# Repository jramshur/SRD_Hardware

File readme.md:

# SRD Hardware

The simultaneous stimulation-and-recording device (SRD) is a wearable, wireless brain-computer interface system designed to train cortical circuits in awake rats. This repository contains design files for the SRD hardware including Eagle PCB files and 3D design files for the enclosure.

Software and firmware for this hardware system can be found in the following repositories:

- https://github.com/jramshur/SRD_Firmware
- https://github.com/jramshur/SRD_GUI

## Description

The simultaneous stimulation-and-recording device (SRD) is a Bluetooth wireless brain-computer interface system designed for use in awake rats. This repository contains design files for the SRD hardware including Eagle PCB files and 3D design files for the enclosure.

### Features
- Cypress Semiconductor PSoC 3 System-on-a-Chip 
- Intan Technologies digital electrophysiology interface chip
- more ...

### System Overview

## Wiki Navigation

* [Home][home]
* [Circuit Design][circuit]
* [PCB Design][pcb]
* [Enclosure][enclosure]
* [Battery][battery]
* [Programming Adaptor][adaptor]

[home]: https://github.com/jramshur/SRD_Hardware/wiki/Home
[circuit]: https://github.com/jramshur/SRD_Hardware/wiki/Circuit
[pcb]: https://github.com/jramshur/SRD_Hardware/wiki/PCB
[enclosure]: https://github.com/jramshur/SRD_Hardware/wiki/Enclosure
[battery]: https://github.com/jramshur/SRD_Hardware/wiki/Battery
[adaptor]: https://github.com/jramshur/SRD_Hardware/wiki/Programming-Adaptor

## Contact Info

John T. Ramshur, PhD  
jramshur@gmail.com  
LinkedIn: [http://www.linkedin.com/in/johnramshur](http://www.linkedin.com/in/johnramshur)  
Blog: [http://www.johnramshur.com](http://www.johnramshur.com)

**Project was part of my PhD work while at:**

Joint Program in Biomedical Engineering  
[University of Memphis](http://www.memphis.edu/bme/)  
[University of Tennessee Health Science Center](http://www.uthsc.edu/bme/)  
Advisor: Amy de Jongh Curry, PhD

Department of Anatomy and Neurobiology  
[University of Tennessee Health Science Center](https://www.uthsc.edu/anatomy-neurobiology/)  
Advisor: Robert S. Waters, PhD

## License

GNU General Public License 3.0

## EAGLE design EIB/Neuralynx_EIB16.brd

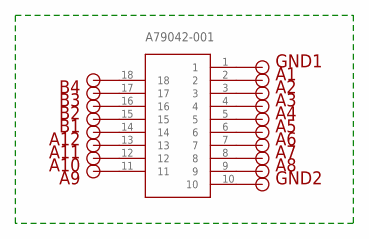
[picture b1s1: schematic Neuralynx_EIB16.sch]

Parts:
A1, A2, A3, A4, A5, A6, A7, A8, A9, A10, A11, A12: VIA_20MILL; VIA_20MIL
A79042-001: A79043-001; OMNETCS-18PIN-SMD
B1, B2, B3, B4: VIA_20MILL; VIA_20MIL
GND1, GND2: VIA_20MILL; VIA_20MIL

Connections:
unnamed: A79042-001.1, GND1.P$1
unnamed: A79042-001.10, GND2.P$1
unnamed: A8.P$1, A79042-001.9
unnamed: A7.P$1, A79042-001.8
unnamed: A6.P$1, A79042-001.7
unnamed: A5.P$1, A79042-001.6
unnamed: A4.P$1, A79042-001.5
unnamed: A3.P$1, A79042-001.4
unnamed: A2.P$1, A79042-001.3
unnamed: A1.P$1, A79042-001.2
unnamed: A9.P$1, A79042-001.11
unnamed: A10.P$1, A79042-001.12
unnamed: A12.P$1, A79042-001.14
unnamed: A79042-001.15, B1.P$1
unnamed: A79042-001.16, B2.P$1
unnamed: A79042-001.17, B3.P$1
unnamed: A79042-001.18, B4.P$1
unnamed: A11.P$1, A79042-001.13

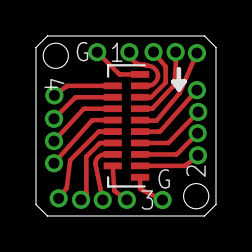
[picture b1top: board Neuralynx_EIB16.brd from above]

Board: 2 copper layers, 10.0 x 10.0 mm, 19 parts (0 on the bottom side), 18 nets.

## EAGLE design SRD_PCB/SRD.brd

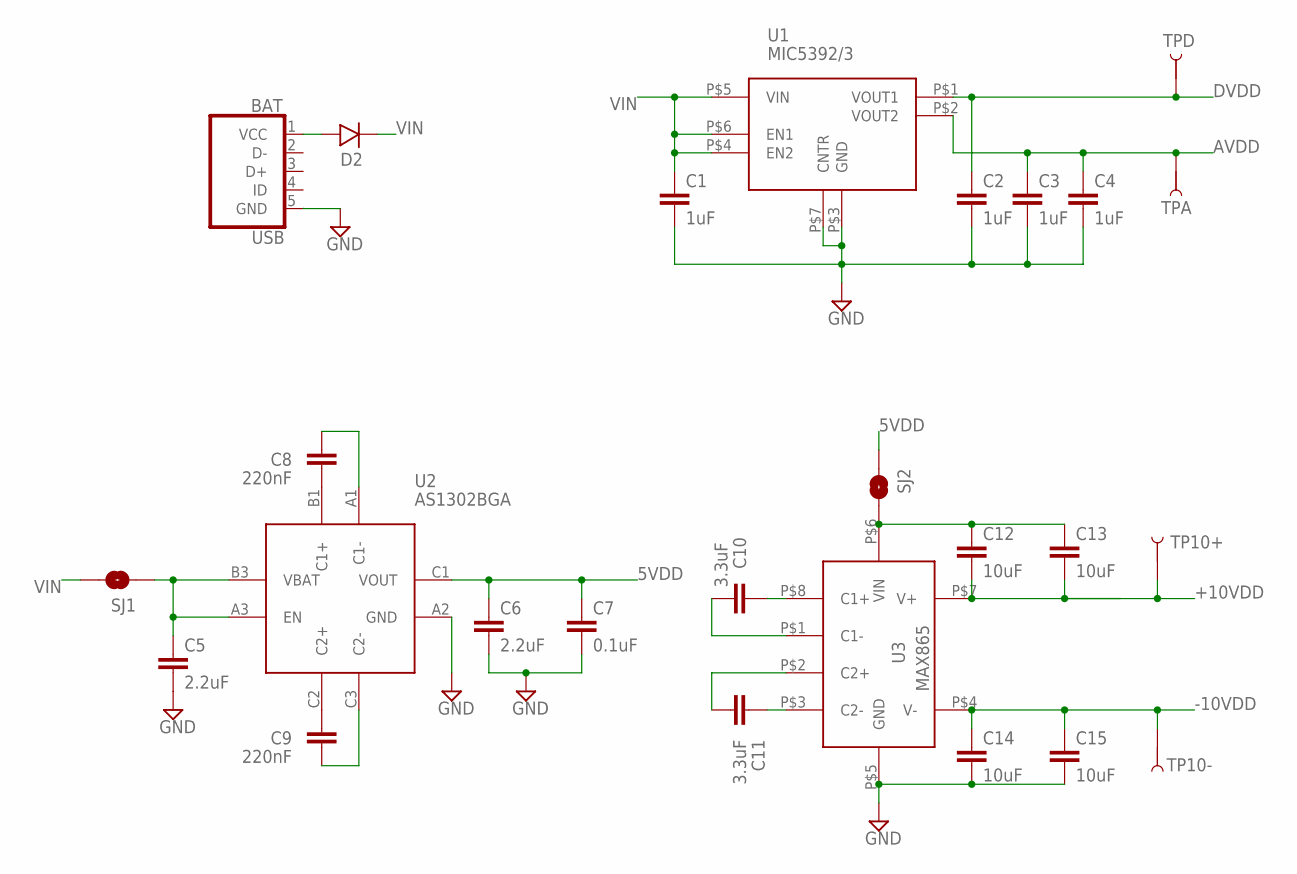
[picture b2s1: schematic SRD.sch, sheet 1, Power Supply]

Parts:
BAT: USB; USB-MICRO-B-TH
C1, C2, C3, C4: 1uF; CAPC1608X90N
C5, C6: 2.2uF; CAPC1608X90N
C7: 0.1uF; CAPC1608X90N
C8, C9: 220nF; CAPC1005X55N
C10, C11: 3.3uF; CAPC2012X100N
C12, C13, C14, C15: 10uF; CAPC2012X100N
D2: DIODE; DO-216AA
SJ1, SJ2: SOLDERJUMPERNO; SJ_2S-NO
TP10+, TP10-: TEST-POINT; PAD1MMX1MM
TPA: TEST-POINT; PAD1MMX1MM
TPD: TEST-POINT; PAD1MMX1MM
U1: MIC5392/3; THIN_DFN
U2: AS1302BGA; BGA9C40P3X3_121X121X63B27N
U3: MAX865; UMAX8

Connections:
5VDD: C6.1, C7.1, SJ2.1, U2.C1 (VOUT)
+10VDD: C12.2, C13.2, TP10+.P$1, U3.P$7 (V+); also elsewhere on the board
-10VDD: C14.1, C15.1, TP10-.P$1, U3.P$4 (V-); also elsewhere on the board
AVDD: C3.1, C4.1, TPA.P$1, U1.P$2 (VOUT2); also elsewhere on the board
DVDD: C2.1, TPD.P$1, U1.P$1 (VOUT1); also elsewhere on the board
GND: BAT.5 (GND), C1.2, C2.2, C3.2, C4.2, C5.2, C6.2, C7.2, C14.2, C15.2, U1.P$3 (GND), U1.P$7 (CNTR), U2.A2 (GND), U3.P$5 (GND); also elsewhere on the board
unnamed: C5.1, SJ1.1, U2.A3 (EN), U2.B3 (VBAT)
unnamed: C12.1, C13.1, SJ2.2, U3.P$6 (VIN)
unnamed: C8.1, U2.A1 (C1-)
unnamed: C9.2, U2.C3 (C2-)
unnamed: C11.1, U3.P$3 (C2-)
unnamed: C11.2, U3.P$2 (C2+)
unnamed: C10.1, U3.P$8 (C1+)
unnamed: C10.2, U3.P$1 (C1-)
unnamed: C8.2, U2.B1 (C1+)
unnamed: C9.1, U2.C2 (C2+)
VBAT: BAT.1 (VCC), D2.A
VIN: C1.1, D2.C, SJ1.2, U1.P$4 (EN2), U1.P$5 (VIN), U1.P$6 (EN1)

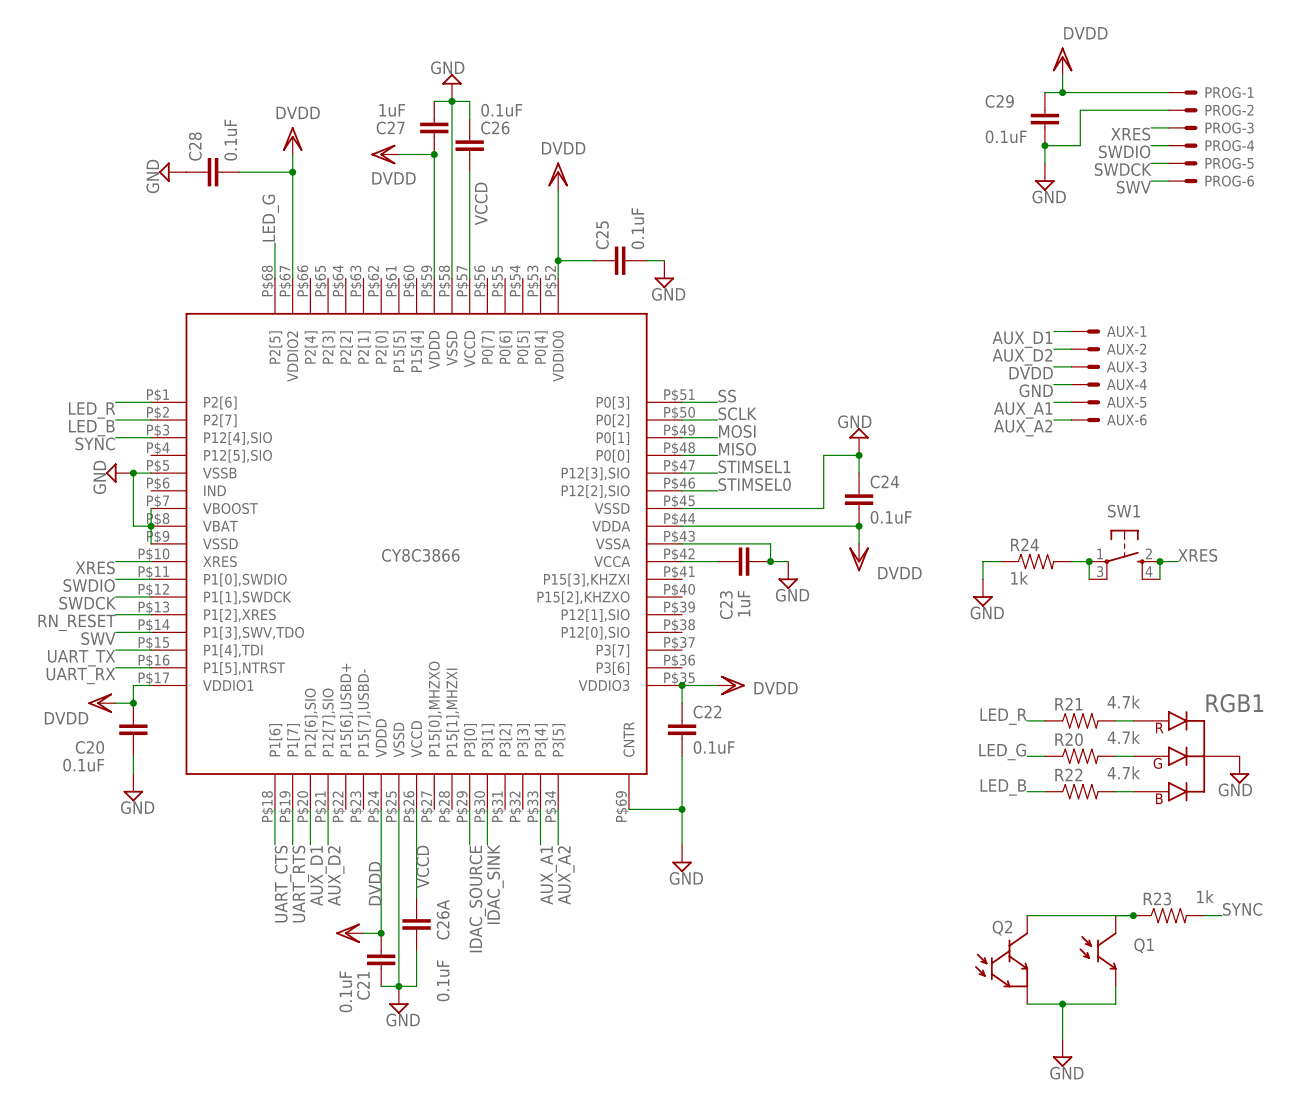
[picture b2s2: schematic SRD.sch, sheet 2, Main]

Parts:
AUX: 52746-6
C20, C21, C22, C24, C25, C26, C26A, C28, C29: 0.1uF; CAPC1005X55N
C23, C27: 1uF; CAPC1005X55N
PROG: 52746-6
Q1: PHOTOTRANSISTOR; MTD8000M3B-T
Q2: PHOTOTRANSISTOR_D; OP501
R20, R21, R22: 4.7k; RESC1005X35N
R23, R24: 1k; RESC1005X35N
RGB1: LED_RGB
SW1: SPST_TACT-KMR2; KMR2
U4: CY8C3866; QFN68_8MM_0.4PITCH

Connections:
AUX_A1: AUX.5, U4.P$33 (P3[4])
AUX_A2: AUX.6, U4.P$34 (P3[5])
AUX_D1: AUX.1, U4.P$20 (P12[6],SIO)
AUX_D2: AUX.2, U4.P$21 (P12[7],SIO)
DVDD: AUX.3, C20.1, C21.1, C22.1, C24.2, C25.1, C27.1, C28.2, C29.1, PROG.1, U4.P$17 (VDDIO1), U4.P$24 (VDDD), U4.P$35 (VDDIO3), U4.P$44 (VDDA), U4.P$52 (VDDIO0), U4.P$59 (VDDD), U4.P$67 (VDDIO2); also elsewhere on the board
GND: AUX.4, C20.2, C21.2, C22.2, C23.2, C24.1, C25.2, C26.2, C26A.1, C27.2, C28.1, C29.2, PROG.2, Q1.E, Q2.E, R24.1, RGB1.P$1 (COM), U4.P$5 (VSSB), U4.P$7 (VBOOST), U4.P$8 (VBAT), U4.P$9 (VSSD), U4.P$25 (VSSD), U4.P$43 (VSSA), U4.P$45 (VSSD), U4.P$58 (VSSD), U4.P$69 (CNTR); also elsewhere on the board
IDAC_SINK: U4.P$30 (P3[1]); also elsewhere on the board
IDAC_SOURCE: U4.P$29 (P3[0]); also elsewhere on the board
LED_B: R22.1, U4.P$2 (P2[7])
LED_G: R20.1, U4.P$68 (P2[5])
LED_R: R21.1, U4.P$1 (P2[6])
MISO: U4.P$48 (P0[0]); also elsewhere on the board
MOSI: U4.P$49 (P0[1]); also elsewhere on the board
unnamed: R21.2, RGB1.P$2 (R)
unnamed: R20.2, RGB1.P$3 (G)
unnamed: R22.2, RGB1.P$4 (B)
unnamed: Q1.C, Q2.C, R23.1
unnamed: R24.2, SW1.1, SW1.3 (P1)
unnamed: C23.1, U4.P$42 (VCCA)
RN_RESET: U4.P$13 (P1[2],XRES); also elsewhere on the board
SCLK: U4.P$50 (P0[2]); also elsewhere on the board
SS: U4.P$51 (P0[3]); also elsewhere on the board
STIMSEL0: U4.P$46 (P12[2],SIO); also elsewhere on the board
STIMSEL1: U4.P$47 (P12[3],SIO); also elsewhere on the board
SWDCK: PROG.5, U4.P$12 (P1[1],SWDCK)
SWDIO: PROG.4, U4.P$11 (P1[0],SWDIO)
SWV: PROG.6, U4.P$14 (P1[3],SWV,TDO)
SYNC: R23.2, U4.P$3 (P12[4],SIO)
UART_CTS: U4.P$18 (P1[6]); also elsewhere on the board
UART_RTS: U4.P$19 (P1[7]); also elsewhere on the board
UART_RX: U4.P$16 (P1[5],NTRST); also elsewhere on the board
UART_TX: U4.P$15 (P1[4],TDI); also elsewhere on the board
VCCD: C26.1, C26A.2, U4.P$26 (VCCD), U4.P$57 (VCCD)
XRES: PROG.3, SW1.2 (S), SW1.4 (S1), U4.P$10 (XRES)

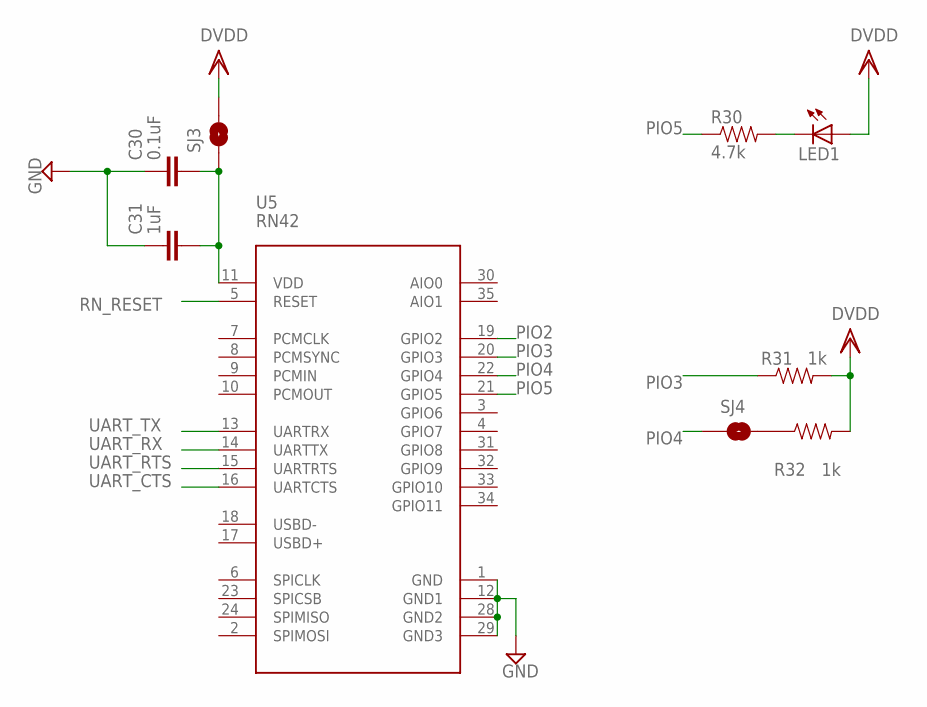
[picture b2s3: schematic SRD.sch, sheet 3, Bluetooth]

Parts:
C30: 0.1uF; CAPC1608X90N
C31: 1uF; CAPC2012X100N
LED1: LED; CHIPLED_0603
R30: 4.7k; RESC1005X35N
R31, R32: 1k; RESC1005X35N
SJ3, SJ4: SOLDERJUMPERNO; SJ_2S-NO
U5: RN42

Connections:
DVDD: LED1.A, R31.2, R32.2, SJ3.2; also elsewhere on the board
GND: C30.1, C31.1, U5.1 (GND), U5.12 (GND1), U5.28 (GND2), U5.29 (GND3); also elsewhere on the board
unnamed: LED1.C, R30.2
unnamed: C30.2, C31.2, SJ3.1, U5.11 (VDD)
unnamed: R32.1, SJ4.2
PIO2: U5.19 (GPIO2)
PIO3: R31.1, U5.20 (GPIO3)
PIO4: SJ4.1, U5.22 (GPIO4)
PIO5: R30.1, U5.21 (GPIO5)
RN_RESET: U5.5 (RESET); also elsewhere on the board
UART_CTS: U5.16 (UARTCTS); also elsewhere on the board
UART_RTS: U5.15 (UARTRTS); also elsewhere on the board
UART_RX: U5.14 (UARTTX); also elsewhere on the board
UART_TX: U5.13 (UARTRX); also elsewhere on the board

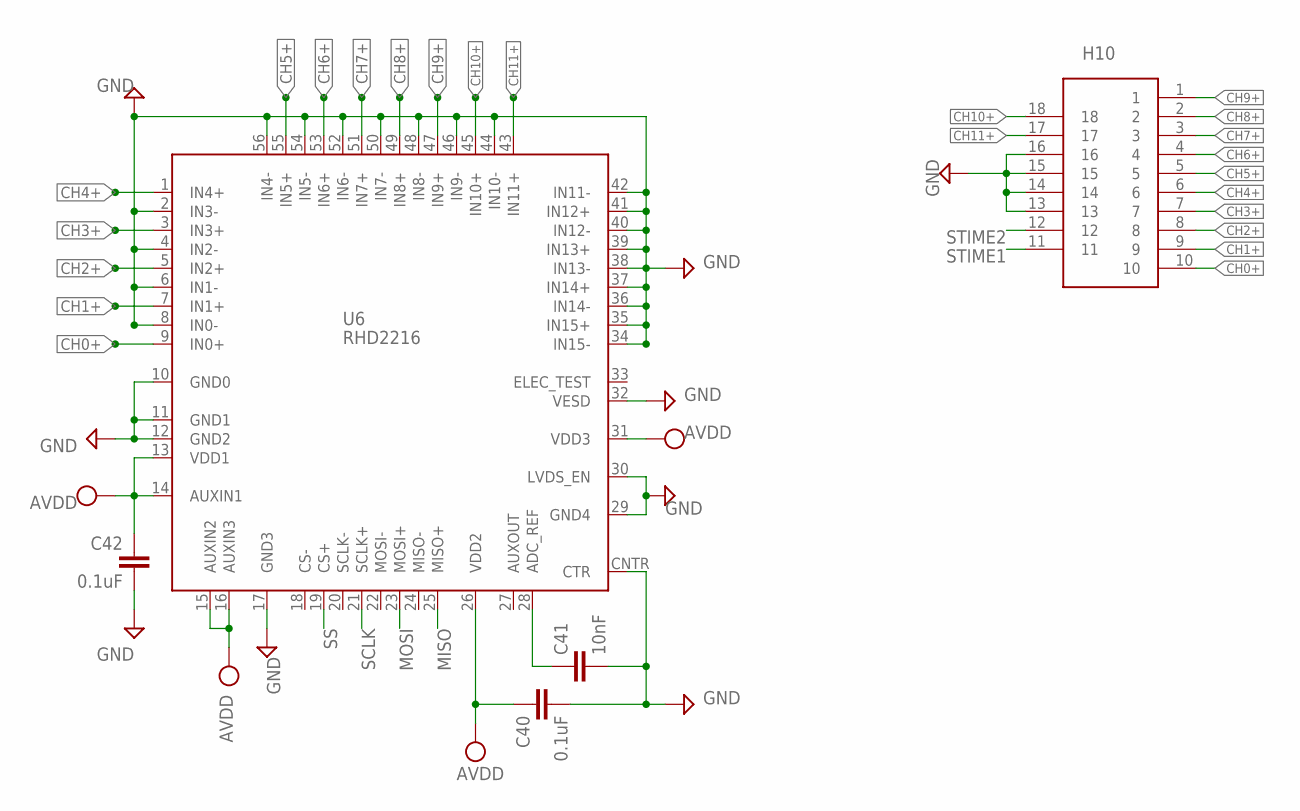
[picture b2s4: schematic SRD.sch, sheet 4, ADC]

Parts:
C40, C42: 0.1uF; CAPC1005X55N
C41: 10nF; CAPC1005X55N
H10: A79043-001; OMNETCS-18PIN-SMD
U6: RHD2216; RHD2000

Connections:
AVDD: C40.1, C42.1, U6.13 (VDD1), U6.14 (AUXIN1), U6.15 (AUXIN2), U6.16 (AUXIN3), U6.26 (VDD2), U6.31 (VDD3); also elsewhere on the board
CH0+: H10.10, U6.9 (IN0+)
CH1+: H10.9, U6.7 (IN1+)
CH2+: H10.8, U6.5 (IN2+)
CH3+: H10.7, U6.3 (IN3+)
CH4+: H10.6, U6.1 (IN4+)
CH5+: H10.5, U6.55 (IN5+)
CH6+: H10.4, U6.53 (IN6+)
CH7+: H10.3, U6.51 (IN7+)
CH8+: H10.2, U6.49 (IN8+)
CH9+: H10.1, U6.47 (IN9+)
CH10+: H10.18, U6.45 (IN10+)
CH11+: H10.17, U6.43 (IN11+)
GND: C40.2, C41.2, C42.2, H10.13, H10.14, H10.15, H10.16, U6.2 (IN3-), U6.4 (IN2-), U6.6 (IN1-), U6.8 (IN0-), U6.10 (GND0), U6.11 (GND1), U6.12 (GND2), U6.17 (GND3), U6.29 (GND4), U6.30 (LVDS_EN), U6.32 (VESD), U6.34 (IN15-), U6.35 (IN15+), U6.36 (IN14-), U6.37 (IN14+), U6.38 (IN13-), U6.39 (IN13+), U6.40 (IN12-), U6.41 (IN12+), U6.42 (IN11-), U6.44 (IN10-), U6.46 (IN9-), U6.48 (IN8-), U6.50 (IN7-), U6.52 (IN6-), U6.54 (IN5-), U6.56 (IN4-), U6.CNTR (CTR); also elsewhere on the board
MISO: U6.25 (MISO+); also elsewhere on the board
MOSI: U6.23 (MOSI+); also elsewhere on the board
unnamed: C41.1, U6.28 (ADC_REF)
SCLK: U6.21 (SCLK+); also elsewhere on the board
SS: U6.19 (CS+); also elsewhere on the board
STIME1: H10.11; also elsewhere on the board
STIME2: H10.12; also elsewhere on the board

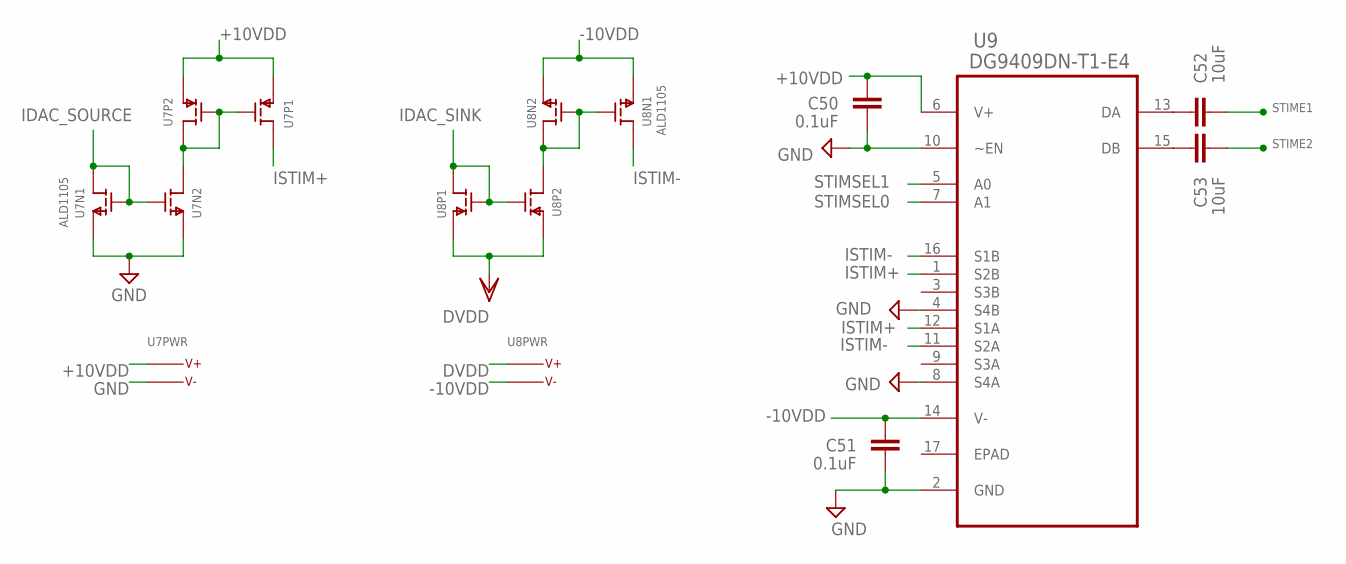
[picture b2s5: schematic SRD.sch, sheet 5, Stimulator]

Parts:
C50, C51: 0.1uF; CAPC1608X90N
C52, C53: 10uF; CAPC2012X100N
U7, U8: ALD1105; SO14MIN
U9: DG9409DN-T1-E4; QFN65P400X400X100-17N

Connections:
+10VDD: C50.1, U7.7 (S), U7.8 (S), U7.11 (V+), U9.6 (V+); also elsewhere on the board
-10VDD: C51.1, U8.3 (S), U8.4 (V-), U8.12 (S), U9.14 (V-); also elsewhere on the board
DVDD: U8.7 (S), U8.8 (S), U8.11 (V+); also elsewhere on the board
GND: C50.2, C51.2, U7.3 (S), U7.4 (V-), U7.12 (S), U9.2 (GND), U9.4 (S4B), U9.8 (S4A), U9.10 (~EN); also elsewhere on the board
IDAC_SINK: U8.5 (D), U8.6 (G), U8.9 (G); also elsewhere on the board
IDAC_SOURCE: U7.1 (D), U7.2 (G), U7.13 (G); also elsewhere on the board
ISTIM+: U7.5 (D), U9.1 (S2B), U9.12 (S1A)
ISTIM-: U8.1 (D), U9.11 (S2A), U9.16 (S1B)
unnamed: C52.1, U9.13 (DA)
unnamed: U7.6 (G), U7.9 (G), U7.10 (D), U7.14 (D)
unnamed: C53.1, U9.15 (DB)
unnamed: U8.2 (G), U8.10 (D), U8.13 (G), U8.14 (D)
STIME1: C52.2; also elsewhere on the board
STIME2: C53.2; also elsewhere on the board
STIMSEL0: U9.7 (A1); also elsewhere on the board
STIMSEL1: U9.5 (A0); also elsewhere on the board

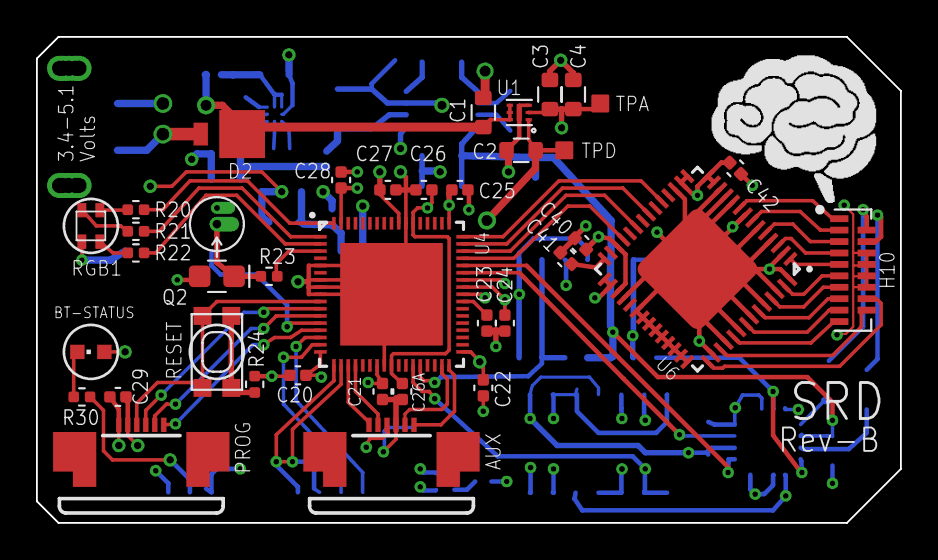
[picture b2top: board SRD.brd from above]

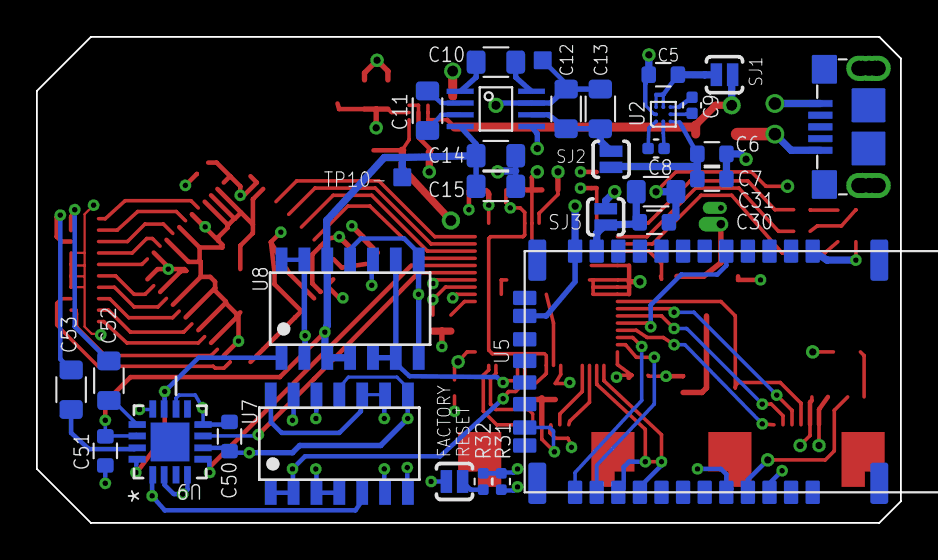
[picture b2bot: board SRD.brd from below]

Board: 4 copper layers, 48.0 x 27.0 mm, 71 parts (32 on the bottom side), 77 nets.

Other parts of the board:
U$1: LOGO_BRAIN

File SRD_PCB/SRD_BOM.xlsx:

Part | Value | Device | H10 | A79043-001 | A79043-001
C20 | 0.1uF | CC0402-N | U7 | ALD1105 | ALD1105
C21 | 0.1uF | CC0402-N | U8 | ALD1105 | ALD1105
C22 | 0.1uF | CC0402-N | U2 | AS1302BGA | AS1302BGA
C24 | 0.1uF | CC0402-N | U4 | CY8C3866 | CY8C3866
C25 | 0.1uF | CC0402-N | U9 | DG9409DN-T1-E4 | DG9409DN-T1-E4
C26 | 0.1uF | CC0402-N | D2 | DIODE | DIODE
C26A | 0.1uF | CC0402-N | RGB1 | LED_RGB | LED_RGB
C28 | 0.1uF | CC0402-N | U3 | MAX865 | MAX865
C29 | 0.1uF | CC0402-N | U1 | MIC5392/3 | MIC5392/3
C40 | 0.1uF | CC0402-N | Q2 | PHOTOTRANSISTOR_D | PHOTOTRANSISTOR_D
C42 | 0.1uF | CC0402-N | U6 | RHD2216 | RHD2216
C7 | 0.1uF | CC0603-N | U5 | RN42 | RN42
C30 | 0.1uF | CC0603-N | SW1 | SPST_TACT-KMR2 | SPST_TACT-KMR2
C50 | 0.1uF | CC0603-N | BAT | USB | USB
C51 | 0.1uF | CC0603-N | Part | Value | Device
C41 | 10nF | CC0402-N | LED1 |  | LED
C12 | 10uF | CC0805-N | Q1 |  | PHOTOTRANSISTOR
C13 | 10uF | CC0805-N
C14 | 10uF | CC0805-N
C15 | 10uF | CC0805-N
C52 | 10uF | CC0805-N
C53 | 10uF | CC0805-N
R23 | 1k | RR0402-N
R24 | 1k | RR0402-N
R31 | 1k | RR0402-N
R32 | 1k | RR0402-N
C23 | 1uF | CC0402-N
C27 | 1uF | CC0402-N
C1 | 1uF | CC0603-N
C2 | 1uF | CC0603-N
C3 | 1uF | CC0603-N
C4 | 1uF | CC0603-N
C31 | 1uF | CC0805-N
C5 | 2.2uF | CC0603-N
C6 | 2.2uF | CC0603-N
C8 | 220nF | CC0402-N
C9 | 220nF | CC0402-N
C10 | 3.3uF | CC0805-N
C11 | 3.3uF | CC0805-N
R20 | 4.7k | RR0402-N
R21 | 4.7k | RR0402-N
R22 | 4.7k | RR0402-N
R30 | 4.7k | RR0402-N
AUX | 52746-6 | 52746-6
PROG | 52746-6 | 52746-6

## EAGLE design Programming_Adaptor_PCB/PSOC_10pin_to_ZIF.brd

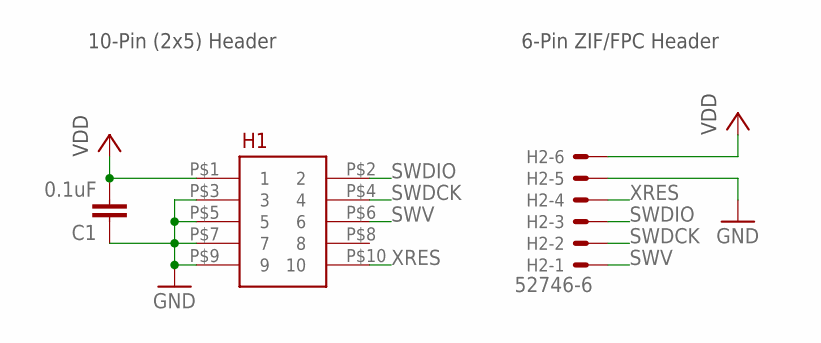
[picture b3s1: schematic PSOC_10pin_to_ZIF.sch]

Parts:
C1: 0.1uF; CAPC1608X90N
H1: 2X5_SMD_HEADER_1.27MM
H2: 52746-6

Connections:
GND: C1.1, H1.P$3 (3), H1.P$5 (5), H1.P$7 (7), H1.P$9 (9), H2.5
SWDCK: H1.P$4 (4), H2.2
SWDIO: H1.P$2 (2), H2.3
SWV: H1.P$6 (6), H2.1
VDD: C1.2, H1.P$1 (1), H2.6
XRES: H1.P$10 (10), H2.4

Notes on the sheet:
10-Pin (2x5) Header
6-Pin ZIF/FPC Header

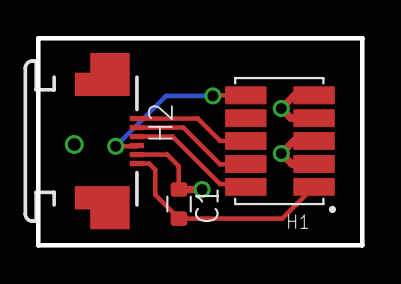
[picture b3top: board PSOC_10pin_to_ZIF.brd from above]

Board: 2 copper layers, 18.0 x 11.5 mm, 3 parts (0 on the bottom side), 6 nets.

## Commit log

2015-09-11 :space_invader: Added .gitattributes
2015-09-11 Initial post-graduate commit
2015-09-11 Added .gitignore and readme
2015-09-13 Added pics
2015-09-14 readme
2016-08-31 Quick update
2016-12-21 Reorganized files
2016-12-21 removed some unwanted files
2016-12-21 updated Sketchup layout file

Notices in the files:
parts and their libraries:
SparkFun-Aesthetics: Licensing: CC v3.0 Share-Alike You are welcome to use this library for commercial purposes.
